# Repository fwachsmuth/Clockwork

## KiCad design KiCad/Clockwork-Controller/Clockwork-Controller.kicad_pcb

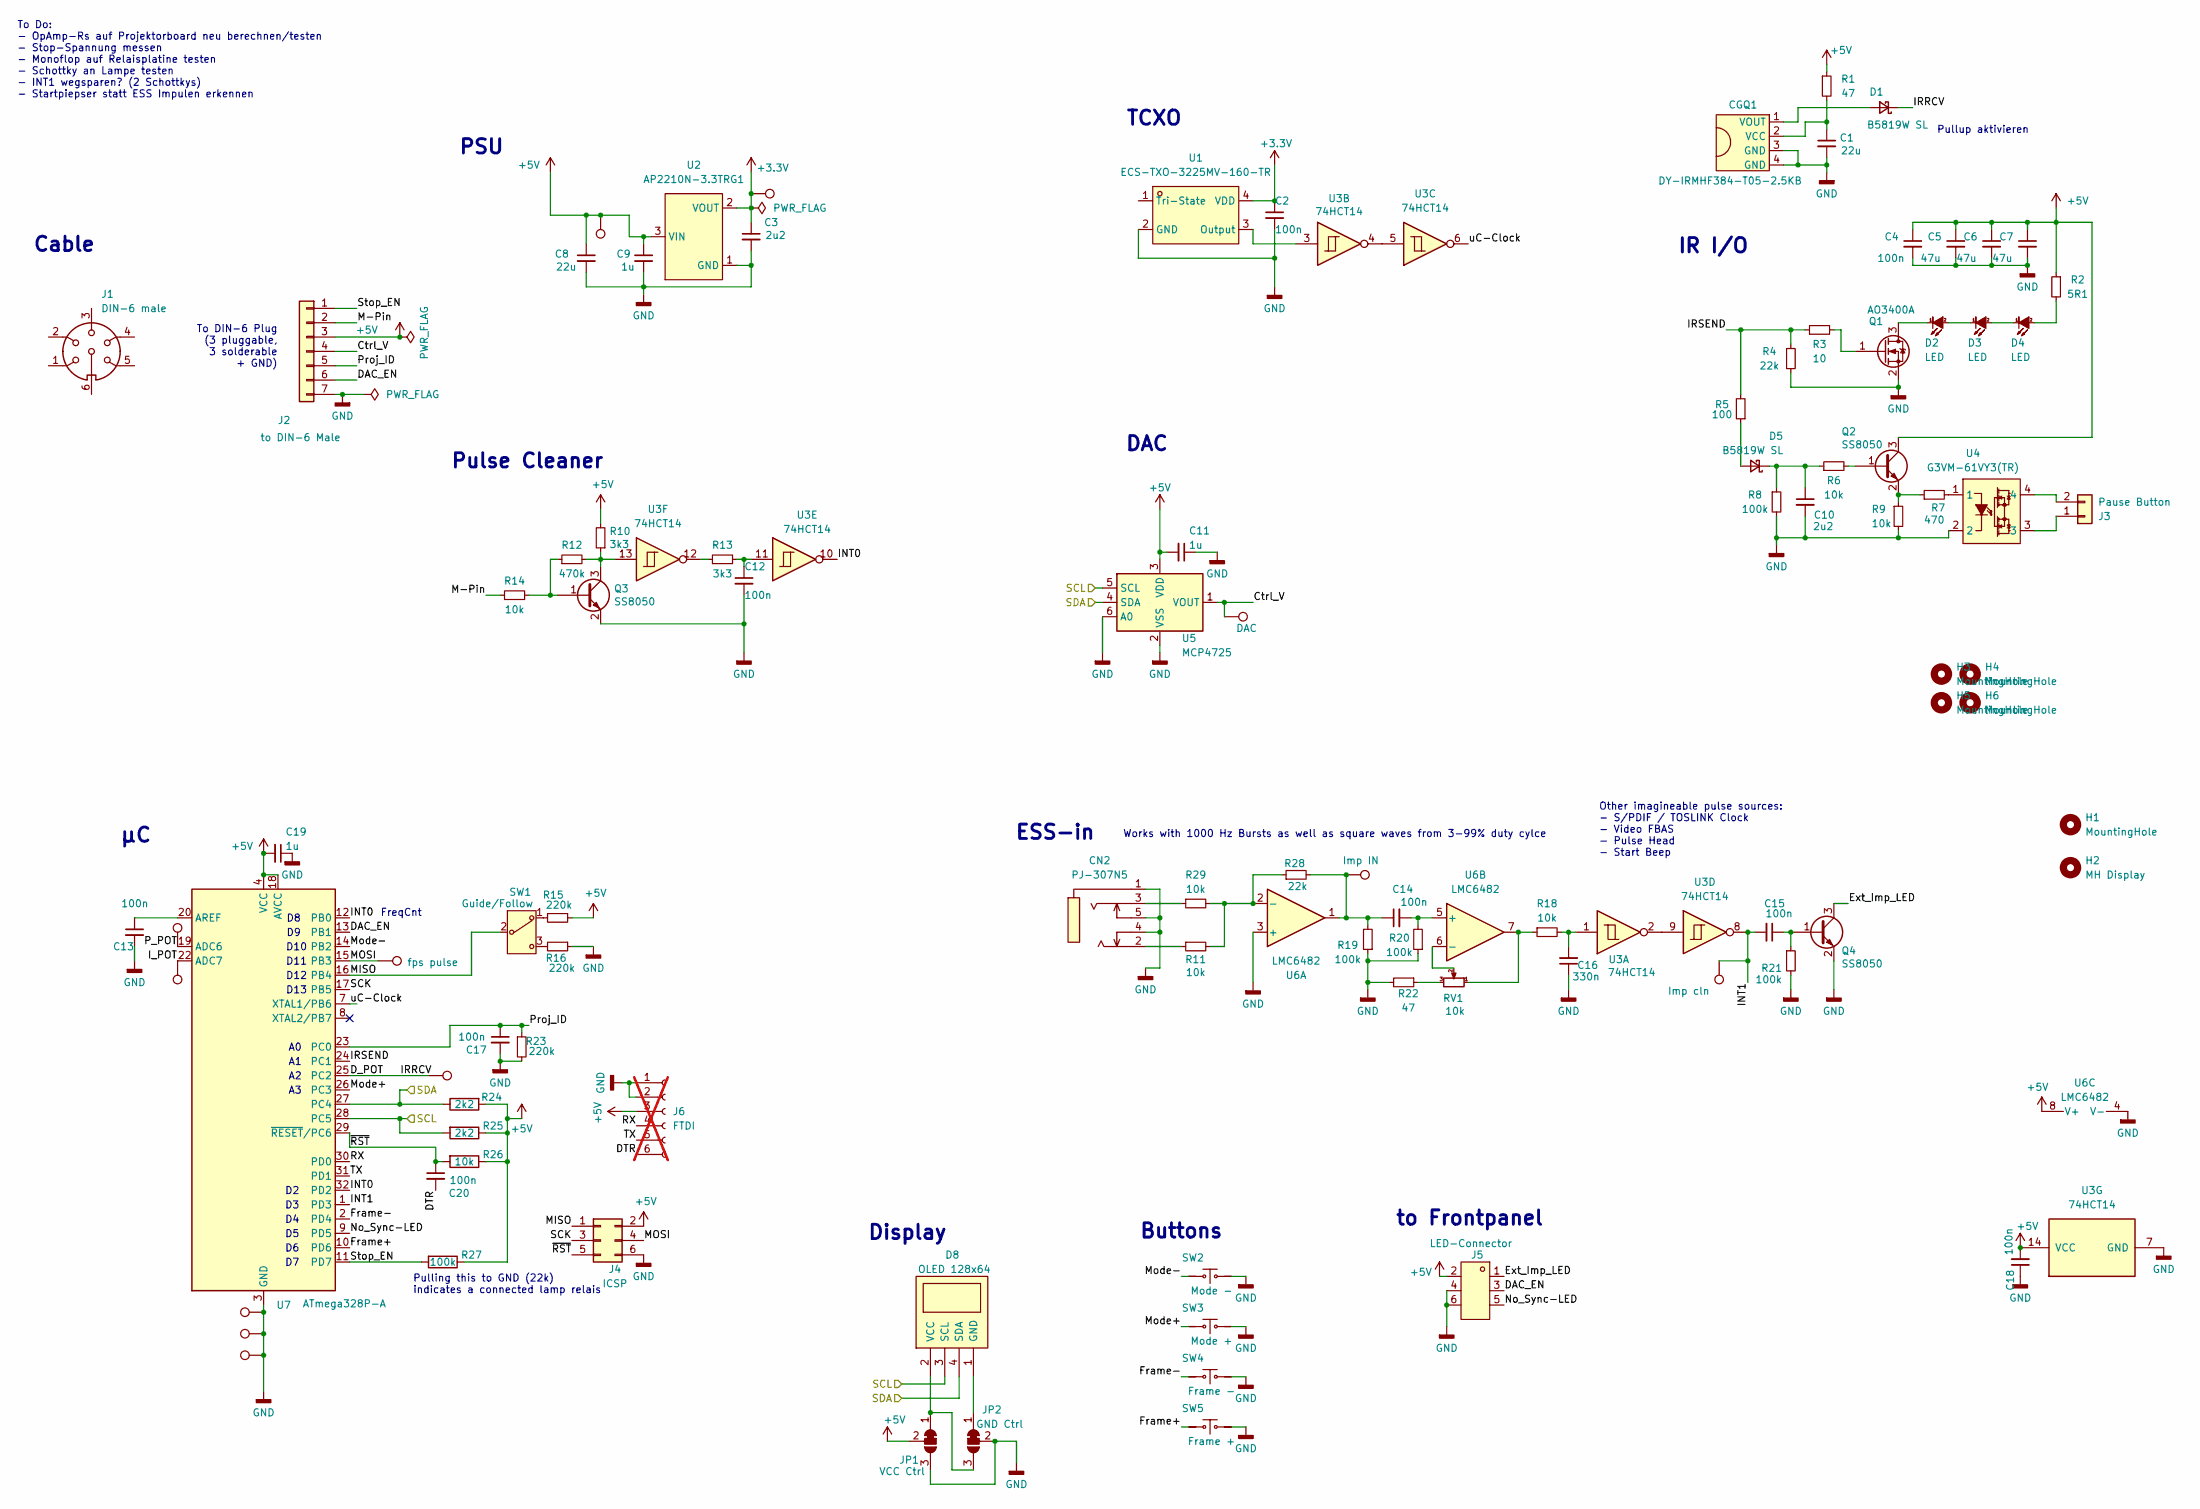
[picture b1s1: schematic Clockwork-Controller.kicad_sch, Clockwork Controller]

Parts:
C1, C8: 22u; C_0805_2012Metric; LCSC C45783
C2, C4, C12, C13, C14, C15, C17, C18, C20: 100n; C_0603_1608Metric; LCSC C14663
C3, C10: 2u2; C_0603_1608Metric; LCSC C23630
C5, C6, C7: 47u; C_1206_3216Metric; LCSC C15008
C9, C11, C19: 1u; C_0603_1608Metric; LCSC C15849
C16: 330n; C_0603_1608Metric; LCSC C1615
CGQ1: DY-IRMHF384-T05-2.5KB; OPTO-SMD_4P-L3.9-W3.4_IRM-H432M3-R8; LCSC Part C7280961
CN2: PJ-307N5; AUDIO-TH_PJ-307N5; LCSC Part C692542
D1, D5: B5819W SL; D_SOD-123; LCSC C8598
D2, D3, D4: LED; LED-SMD_XYC-IRA4335A65-X4; LCSC C2920776
D8: OLED 128x64; HDR-TH_4P-P2.54-V-F; LCSC C42163122
H1: MountingHole; Kabelbinder 4mm
H2: MH Display; MountingHole_2.2mm_M2_DIN965
H3, H4, H5, H6: MountingHole; MountingHole_3.2mm_M3_DIN965
J1: DIN-6 male
J2: to DIN-6 Male; CONN-TH_S7B-XH-A-LF-SN; LCSC C157916
J3: Pause Button; CONN-TH_2P-P2.54_MX128-2.54-GN01-02P-CU-Y-A; LCSC C918120
J4: ICSP; PinHeader_2x03_P2.54mm_Vertical_displaced
J5: LED-Connector; HDR-TH_6P-P2.00-V-F-R2-C3-S2.00-2; LCSC C7499367
J6: FTDI; PinHeader_1x06_P2.54mm_Vertical; not fitted
JP1: VCC Ctrl; SolderJumper-3_P1.3mm_Bridged2Bar12_RoundedPad1.0x1.5mm
JP2: GND Ctrl; SolderJumper-3_P1.3mm_Bridged2Bar12_RoundedPad1.0x1.5mm
Q1: AO3400A; SOT-23; LCSC C20917
Q2, Q3, Q4: SS8050; SOT-23; LCSC C2146
R1, R22: 47; R_0603_1608Metric; LCSC C23182
R2: 5R1; R_0805_2012Metric; LCSC C17724
R3: 10; R_0603_1608Metric; LCSC C22859
R4, R28: 22k; R_0603_1608Metric; LCSC C31850
R5: 100; R_0603_1608Metric; LCSC C22775
R6, R9, R11, R14, R18, R26, R29: 10k; R_0603_1608Metric; LCSC C25804
R7: 470; R_0603_1608Metric; LCSC C23179
R8, R19, R20, R21, R27: 100k; R_0603_1608Metric; LCSC C25803
R10, R13: 3k3; R_0603_1608Metric; LCSC C22978
R12: 470k; R_0603_1608Metric; LCSC C23178
R15, R16, R23: 220k; R_0603_1608Metric; LCSC C22961
R24, R25: 2k2; R_0603_1608Metric; LCSC C4190
RV1: 10k; RES-SMD_RK10J11R0A0H_fixed; LCSC C470766
SW1: Guide/Follow; SW-TH_SS-12D11G4R; LCSC C843370
SW2: Mode -; SW-SMD_4P-L6.0-W6.0-P4.50-LS9.0-H11.5; LCSC C455123
SW3: Mode +; SW-SMD_4P-L6.0-W6.0-P4.50-LS9.0-H11.5; LCSC C455123
SW4: Frame -; SW-SMD_4P-L6.0-W6.0-P4.50-LS9.0-H11.5; LCSC C455123
SW5: Frame +; SW-SMD_4P-L6.0-W6.0-P4.50-LS9.0-H11.5; LCSC C455123
TP1: 3V3; TestPoint_THTPad_1.5x1.5mm_Drill0.7mm
TP2: 5V; TestPoint_THTPad_1.5x1.5mm_Drill0.7mm
TP3, TP4, TP12: GND; TestPoint_THTPad_1.5x1.5mm_Drill0.7mm
TP5: DAC; TestPoint_THTPad_1.5x1.5mm_Drill0.7mm
TP6: P; TestPoint_THTPad_1.5x1.5mm_Drill0.7mm
TP7: I; TestPoint_THTPad_1.5x1.5mm_Drill0.7mm
TP8: fps pulse; TestPoint_THTPad_1.5x1.5mm_Drill0.7mm
TP9: Imp IN; TestPoint_THTPad_1.5x1.5mm_Drill0.7mm
TP10: Imp cln; TestPoint_THTPad_1.5x1.5mm_Drill0.7mm
TP11: D; TestPoint_THTPad_1.5x1.5mm_Drill0.7mm
U1: ECS-TXO-3225MV-160-TR; Crystal_SMD_3225-4Pin_3.2x2.5mm; LCSC C2442664
U2: AP2210N-3.3TRG1; SOT-23-3; LCSC Part C155508
U3: 74HCT14; TSSOP-14_4.4x5mm_P0.65mm; LCSC C5968
U4: G3VM-61VY3(TR); SOP-4_L3.9-W4.4-P2.54-LS7.0-BR; LCSC Part C2152318
U5: MCP4725; SOT-23-6; LCSC C144198
U6: LMC6482; SOIC-8_3.9x4.9mm_P1.27mm; LCSC C12620
U7: ATmega328P-A; TQFP-32_7x7mm_P0.8mm; LCSC C14877

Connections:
+3.3V: C2.1, C3.1, TP1.1, U1.4 (VDD), U2.2 (VOUT)
+5V: C4.1, C5.1, C6.1, C7.1, C8.1, C9.1, C11.2, C18.2, C19.2, J2.3, J4.2, J5.2, J6.3, JP1.2 (C), Q2.3 (C), R1.1, R2.1, R10.2, R15.1, R24.2, R25.1, R26.1, R27.1, TP2.1, U2.3 (VIN), U3.14 (VCC), U5.3 (VDD), U6.8 (V+), U7.4 (VCC), U7.6 (VCC), U7.18 (AVCC)
/Ctrl_V: J2.4, TP5.1, U5.1 (VOUT)
/DAC_EN: J2.6, J5.3, U7.13 (PB1)
/DTR: C20.2, J6.6
/D_POT: D1.1 (K), TP11.1, U7.25 (PC2)
/Ext_Imp_LED: J5.1, Q4.3 (C)
/Frame+: SW5.1, SW5.2, U7.10 (PD6)
/Frame-: SW4.1, SW4.2, U7.2 (PD4)
/INT0: U3.10, U7.12 (PB0), U7.32 (PD2)
/INT1: C15.2, TP10.1, U3.8, U7.1 (PD3)
/IRSEND: R3.1, R4.1, R5.2, U7.24 (PC1)
/I_POT: TP7.1, U7.22 (ADC7)
/M-Pin: J2.2, R14.1
/MISO: J4.1, SW1.2, U7.16 (PB4)
/MOSI: J4.4, TP8.1, U7.15 (PB3)
/Mode+: SW3.1, SW3.2, U7.26 (PC3)
/Mode-: SW2.1, SW2.2, U7.14 (PB2)
/No_Sync-LED: J5.5, U7.9 (PD5)
/P_POT: TP6.1, U7.19 (ADC6)
/Proj_ID: C17.1, J2.5, R23.1, U7.23 (PC0)
/RX: J6.4, U7.30 (PD0)
/SCK: J4.3, U7.17 (PB5)
/SCL: D8.3 (SCL), R25.2, U5.5 (SCL), U7.28 (PC5)
/SDA: D8.4 (SDA), R24.1, U5.4 (SDA), U7.27 (PC4)
/Stop_EN: J2.1, R27.2, U7.11 (PD7)
/TX: J6.5, U7.31 (PD1)
/uC-Clock: U3.6, U7.7 (XTAL1/PB6)
/~RST: C20.1, J4.5, R26.2, U7.29 (~RESET/PC6)
GND: C1.2, C2.2, C3.2, C4.2, C5.2, C6.2, C7.2, C8.2, C9.2, C10.2, C11.1, C12.2, C13.2, C16.1, C17.2, C18.1, C19.1, CGQ1.3 (GND), CGQ1.4 (GND), CN2.1, CN2.4, CN2.5, J2.7, J4.6, J5.4, J5.6, J6.1, J6.2, JP1.3 (B), JP2.2 (C), Q1.2 (S), Q3.2 (E), Q4.2 (E), R4.2, R8.2, R9.2, R16.1, R19.1, R20.1, R21.2, R22.2, R23.2, SW2.3, SW2.4, SW3.3, SW3.4, SW4.3, SW4.4, SW5.3, SW5.4, TP3.1, TP4.1, TP12.1, U1.2 (GND), U2.1 (GND), U3.7 (GND), U4.2, U5.2 (VSS), U5.6 (A0), U6.3 (+), U6.4 (V-), U7.3 (GND), U7.5 (GND), U7.21 (GND)
unnamed: C12.1, R13.2, U3.11
unnamed: C14.1, R19.2, R28.2, TP9.1, U6.1
unnamed: C16.2, R18.2, U3.1
unnamed: C1.1, CGQ1.2 (VCC), R1.2
unnamed: CGQ1.1 (VOUT), D1.2 (A)
unnamed: CN2.2, R11.1
unnamed: CN2.3, R29.1
unnamed: D2.2 (A), D3.1 (K)
unnamed: D2.1 (K), Q1.3 (D)
unnamed: D3.2 (A), D4.1 (K)
unnamed: D4.2 (A), R2.2
unnamed: D5.2 (A), R5.1
unnamed: C10.1, D5.1 (K), R6.1, R8.1
unnamed: D8.1 (GND), JP2.1 (A)
unnamed: D8.2 (VCC), JP1.1 (A), JP2.3 (B)
unnamed: J3.1, U4.3
unnamed: J3.2, U4.4
unnamed: Q1.1 (G), R3.2
unnamed: Q2.1 (B), R6.2
unnamed: Q2.2 (E), R7.1, R9.1
unnamed: Q3.1 (B), R12.1, R14.2
unnamed: Q3.3 (C), R10.1, R12.2, U3.13
unnamed: C15.1, Q4.1 (B), R21.1
unnamed: R7.2, U4.1
unnamed: R13.1, U3.12
unnamed: R15.2, SW1.1
unnamed: R16.2, SW1.3
unnamed: R18.1, RV1.1, U6.7
unnamed: R22.1, RV1.3
unnamed: U1.3 (Output), U3.3
unnamed: U3.2, U3.9
unnamed: U3.4, U3.5
unnamed: R11.2, R28.1, R29.2, U6.2 (-)
unnamed: C14.2, R20.2, U6.5 (+)
unnamed: RV1.2, U6.6 (-)
unnamed: C13.1, U7.20 (AREF)

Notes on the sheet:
D10
Pullup aktivieren
Display
Other imagineable pulse sources: - S/PDIF / TOSLINK Clock - Video FBAS - Pulse Head - Start Beep
D13
Buttons
to Frontpanel
Pulling this to GND (22k) indicates a connected lamp relais
To Do: - OpAmp-Rs auf Projektorboard neu berechnen/testen - Stop-Spannung messen - Monoflop auf Relaisplatine testen - Schottky an Lampe testen - INT1 wegsparen? (2 Schottkys) - Startpiepser statt ESS Impulen erkennen
Pulse Cleaner
Cable
D11
TCXO
DAC
Works with 1000 Hz Bursts as well as square waves from 3-99% duty cylce
FreqCnt
ESS-in
PSU
D12
To DIN-6 Plug (3 pluggable, 3 solderable + GND)
IR I/O

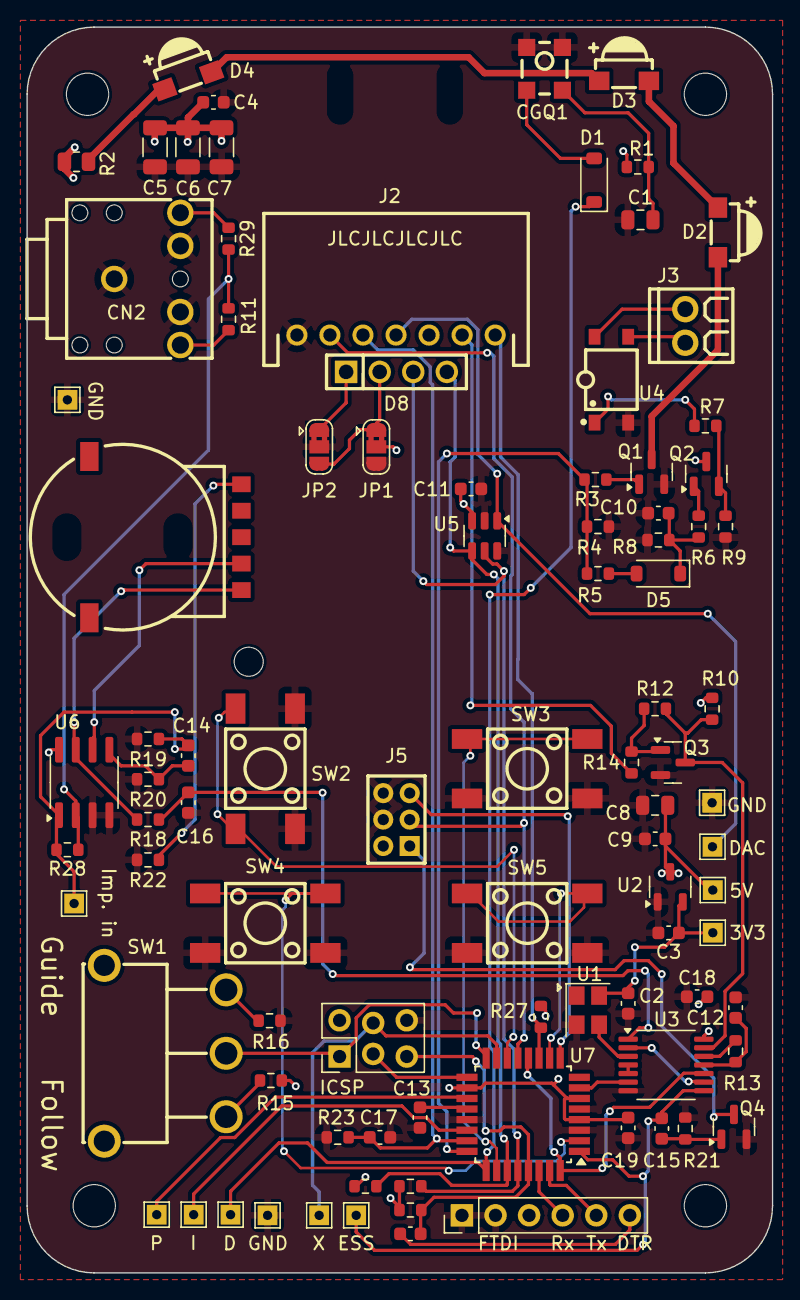
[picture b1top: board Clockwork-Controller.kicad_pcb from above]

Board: 2 copper layers, 56.4 x 94.2 mm, 98 parts (0 on the bottom side), 66 nets.

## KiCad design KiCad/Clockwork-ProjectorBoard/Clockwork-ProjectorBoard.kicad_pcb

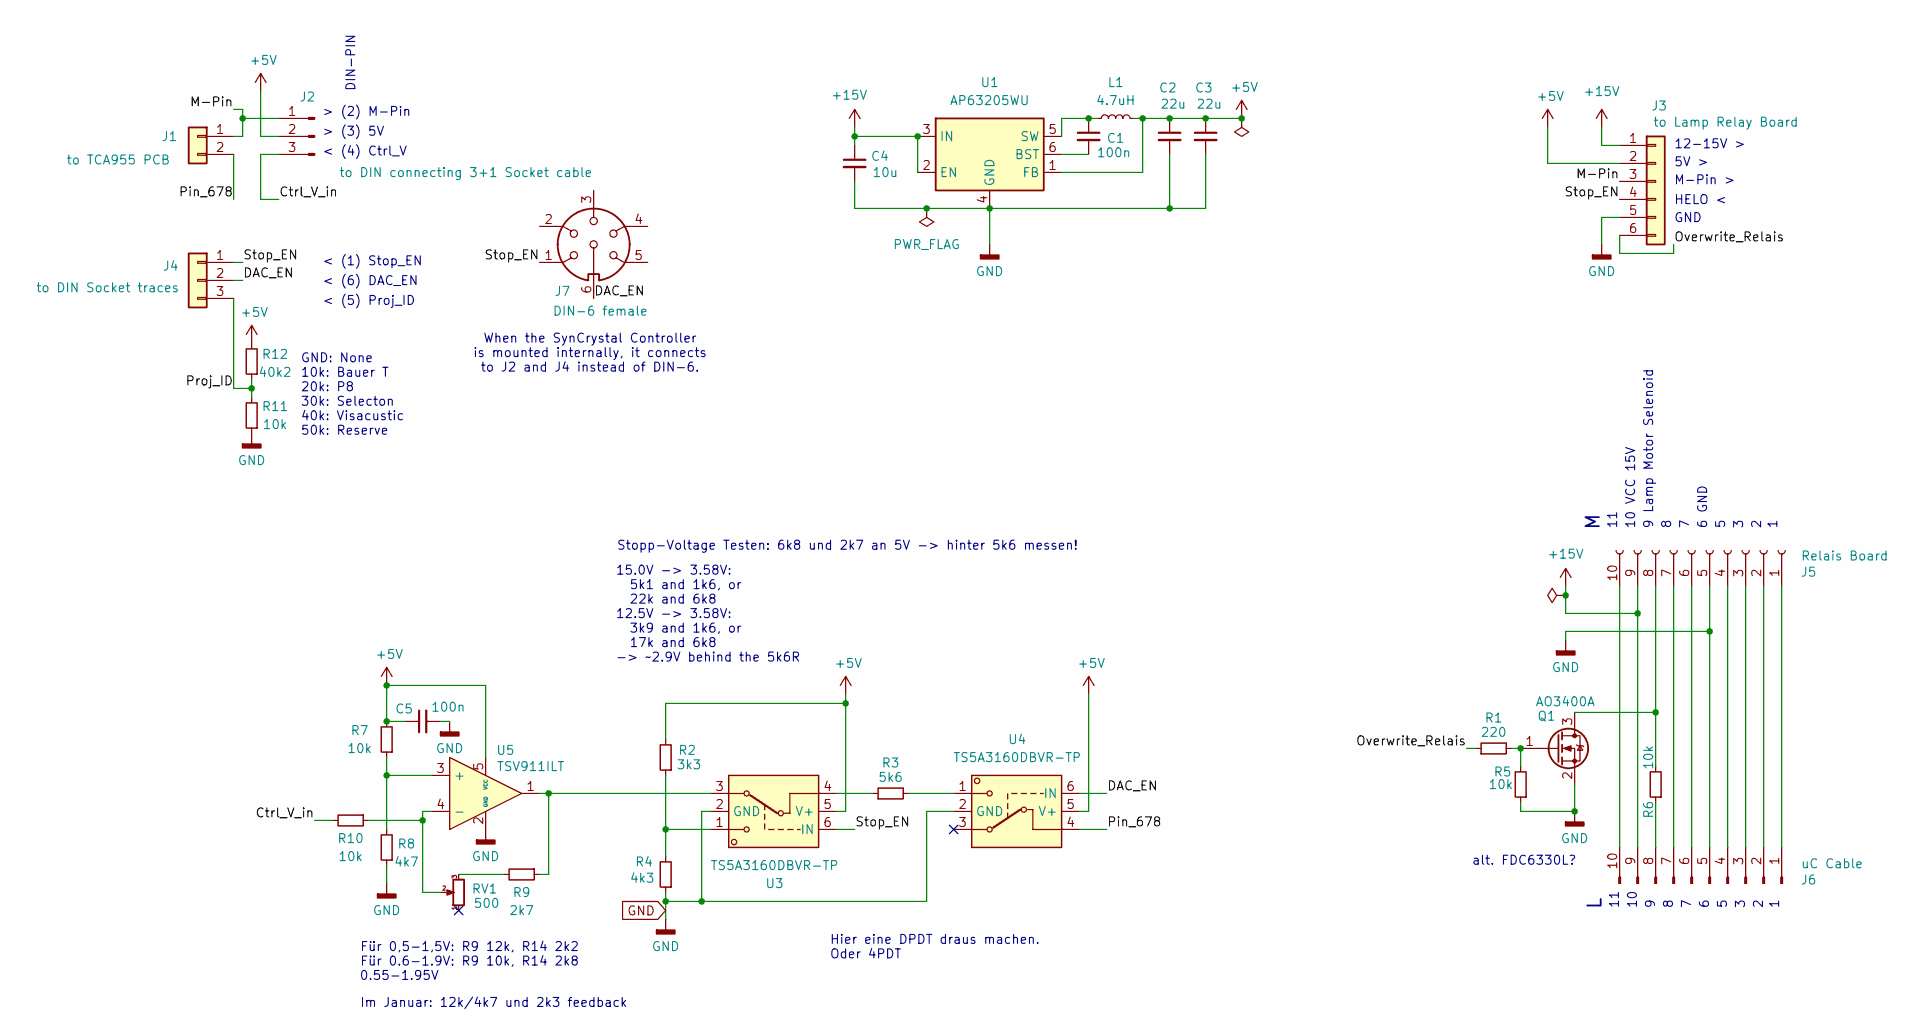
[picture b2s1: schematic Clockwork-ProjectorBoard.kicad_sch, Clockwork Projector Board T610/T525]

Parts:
C1, C5: 100n; C_0603_1608Metric; LCSC C14663
C2, C3: 22u; C_0603_1608Metric; LCSC C45783
C4: 10u; C_0603_1608Metric; LCSC C15850
J1: to TCA955 PCB; CONN-TH_2P-P2.54_ZX-XH2.54-2PZZ-Y; LCSC C22388684
J2: to DIN connecting 3+1 Socket cable; PinHeader_1x03_P2.54mm_Vertical_BAUER; LCSC C6332196
J3: to Lamp Relay Board; CONN-TH_6P-P2.54_ZX-XH2.54-6PZZ-R; LCSC C22388628
J4: to DIN Socket traces; CONN-TH_ZX-XH2.54-3PZZ-Y; LCSC C22388685
J5: Relais Board; HDR-TH_10P-P2.54-H-F-W10.0-N; LCSC C2897392
J6: uC Cable; HDR-TH_10P-P2.54-H-M-W10.4_flipped; LCSC C3012231
J7: DIN-6 female
L1: 4.7uH; IND-SMD_L3.0-W3.0; LCSC C527613
Q1: AO3400A; SOT-23; LCSC C20917
R1: 220; R_0603_1608Metric; LCSC C22962
R2: 3k3; R_0603_1608Metric
R3: 5k6; R_0603_1608Metric; LCSC C23189
R4: 4k3; R_0603_1608Metric
R5, R6, R7, R10: 10k; R_0603_1608Metric; LCSC C25804
R8: 4k7; R_0603_1608Metric; LCSC C23162
R9: 2k7; R_0603_1608Metric; LCSC C13167
R11: 10k; R_0402_1005Metric; LCSC C25744
R12: 40k2; R_0402_1005Metric; LCSC C137983
RV1: 500; RES-ADJ-SMD_3P-L3.8-W3.7_VGF39NCHXT; LCSC C720649
U1: AP63205WU; TSOT-23-6; LCSC C2071056
U3, U4: TS5A3160DBVR-TP; SOT-23-6_L2.9-W1.6-P0.95-LS2.8-BR; LCSC C42411033
U5: TSV911ILT; SOT-23-5_L2.9-W1.6-P0.95-LS2.8-BR; LCSC C672321

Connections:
+5V: C2.1, C3.1, C5.1, J2.2, J3.2, L1.2, R2.2, R7.2, R12.2, U1.1 (FB), U3.5 (V+), U4.5 (V+), U5.5 (VCC)
+15V: C4.1, J3.1, J5.9, J6.9, U1.2 (EN), U1.3 (IN)
/Ctrl_V_in: J2.3, R10.2
/DAC_EN: J4.2, J7.6, U4.6 (IN)
/M-Pin: J1.1, J2.1, J3.3
/Overwrite_Relais: J3.6, R1.1
/Pin_678: J1.2, U4.4
/Proj_ID: J4.3, R11.2, R12.1
/Stop_EN: J3.4, J4.1, J7.1, U3.6 (IN)
GND: C2.2, C3.2, C4.2, C5.2, J3.5, J5.5, J6.5, Q1.2 (S), R4.1, R5.1, R8.1, R11.1, U1.4 (GND), U3.2 (GND), U4.2 (GND), U5.2 (GND)
unnamed: J5.1, J6.1
unnamed: J5.2, J6.2
unnamed: J5.3, J6.3
unnamed: J5.4, J6.4
unnamed: J5.6, J6.6
unnamed: J5.7, J6.7
unnamed: J5.8, Q1.3 (D), R6.2
unnamed: J5.10, J6.10
unnamed: J6.8, R6.1
unnamed: Q1.1 (G), R1.2, R5.2
unnamed: R2.1, R4.2, U3.1
unnamed: R3.1, U3.4
unnamed: R3.2, U4.1
unnamed: R9.1, U3.3, U5.1
unnamed: R9.2, RV1.3
unnamed: C1.2, U1.6 (BST)
unnamed: C1.1, L1.1, U1.5 (SW)
unnamed: R7.1, R8.2, U5.3 (+)
unnamed: R10.1, RV1.2, U5.4 (-)

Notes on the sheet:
Hier eine DPDT draus machen. Oder 4PDT
5V >
0.55-1.95V
M-Pin >
Für 0,5-1,5V: R9 12k, R14 2k2 Für 0.6-1.9V: R9 10k, R14 2k8
HELO <
When the SynCrystal Controller is mounted internally, it connects to J2 and J4 instead of DIN-6.
6 GND
> (3) 5V
< (6) DAC_EN
Im Januar: 12k/4k7 und 2k3 feedback
> (2) M-Pin
DIN-PIN
GND: None 10k: Bauer T 20k: P8 30k: Selecton 40k: Visacustic 50k: Reserve
10 VCC 15V
< (5) Proj_ID
alt. FDC6330L?
< (4) Ctrl_V
15.0V -> 3.58V: 5k1 and 1k6, or 22k and 6k8 12.5V -> 3.58V: 3k9 and 1k6, or 17k and 6k8 -> ~2.9V behind the 5k6R
< (1) Stop_EN
GND
12-15V >
9 Lamp Motor Selenoid
Stopp-Voltage Testen: 6k8 und 2k7 an 5V -> hinter 5k6 messen!

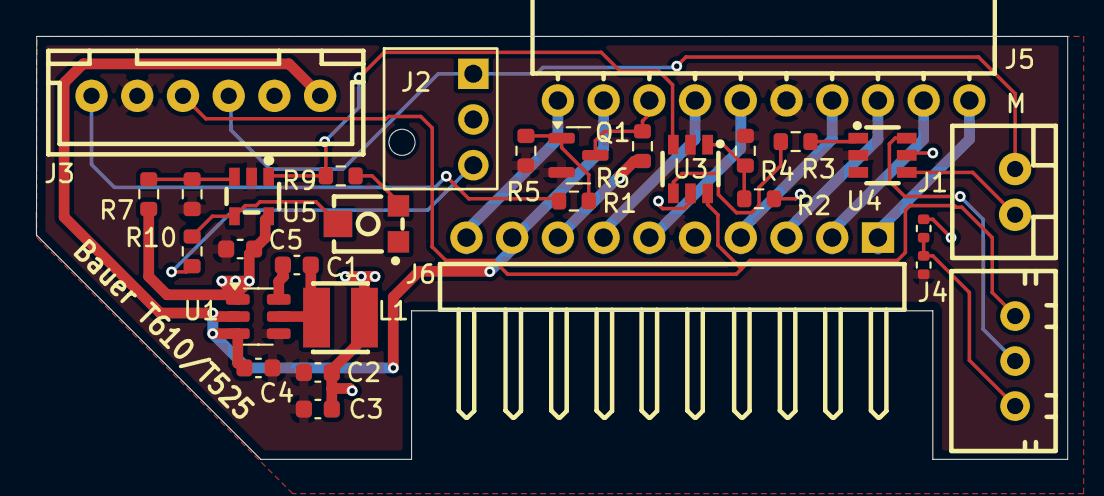
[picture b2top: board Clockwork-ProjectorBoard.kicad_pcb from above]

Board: 2 copper layers, 57.3 x 23.5 mm, 30 parts (0 on the bottom side), 29 nets.

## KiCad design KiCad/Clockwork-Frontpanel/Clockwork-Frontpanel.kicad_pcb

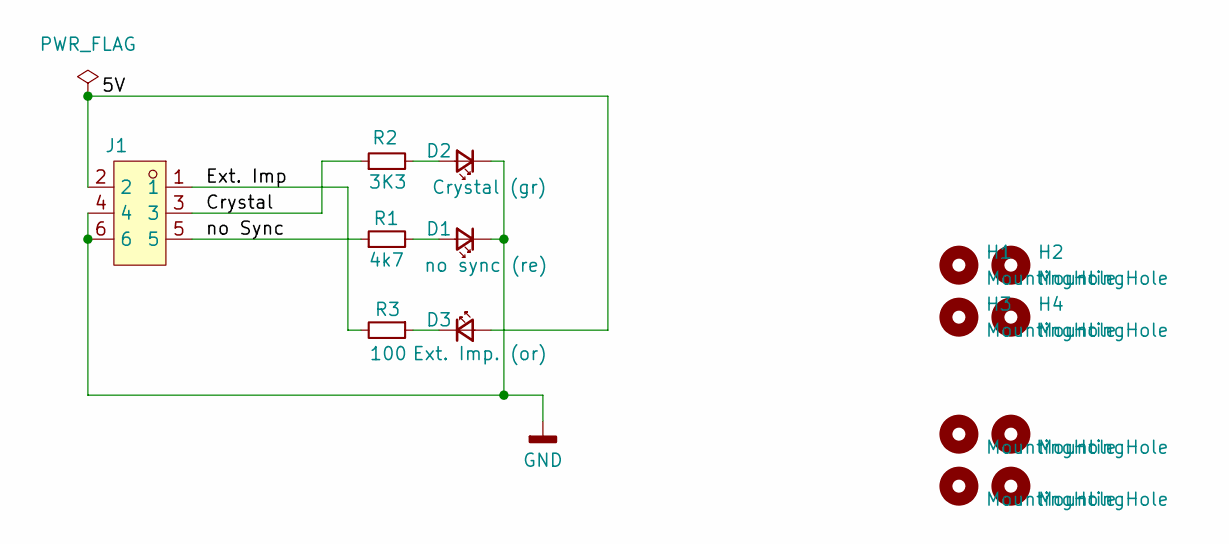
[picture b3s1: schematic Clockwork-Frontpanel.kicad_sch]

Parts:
D1: no sync (re); LED-SMD_L3.2-W1.6-RD-EH-3_kicad; LCSC C2892757
D2: Crystal (gr); LED-SMD_L3.2-W1.6-RD-EH-3_kicad; LCSC C2980185
D3: Ext. Imp. (or); LED-SMD_L3.2-W1.6-RD-EH-3_kicad; LCSC C424133
H1, H2, H3, H4: MountingHole; MountingHole_3.2mm_M3_DIN965
H5, H6, H7, H8: MountingHole; MountingHole_3.5mm_M3
J1: HDR-SMD_6P-P2.00-V-M-R2-C3-LS6.5_flipped; LCSC Part C3294482
R1: 4k7; R_0603_1608Metric
R2: 3K3; R_0603_1608Metric; LCSC C22978
R3: 100; R_0603_1608Metric

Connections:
/5V: D3.2 (A), J1.2
/Crystal: J1.3, R2.1
/Ext. Imp: J1.1, R3.2
/no Sync: J1.5, R1.1
GND: D1.1 (K), D2.1 (K), J1.4, J1.6
unnamed: D1.2 (A), R1.2
unnamed: D2.2 (A), R2.2
unnamed: D3.1 (K), R3.1

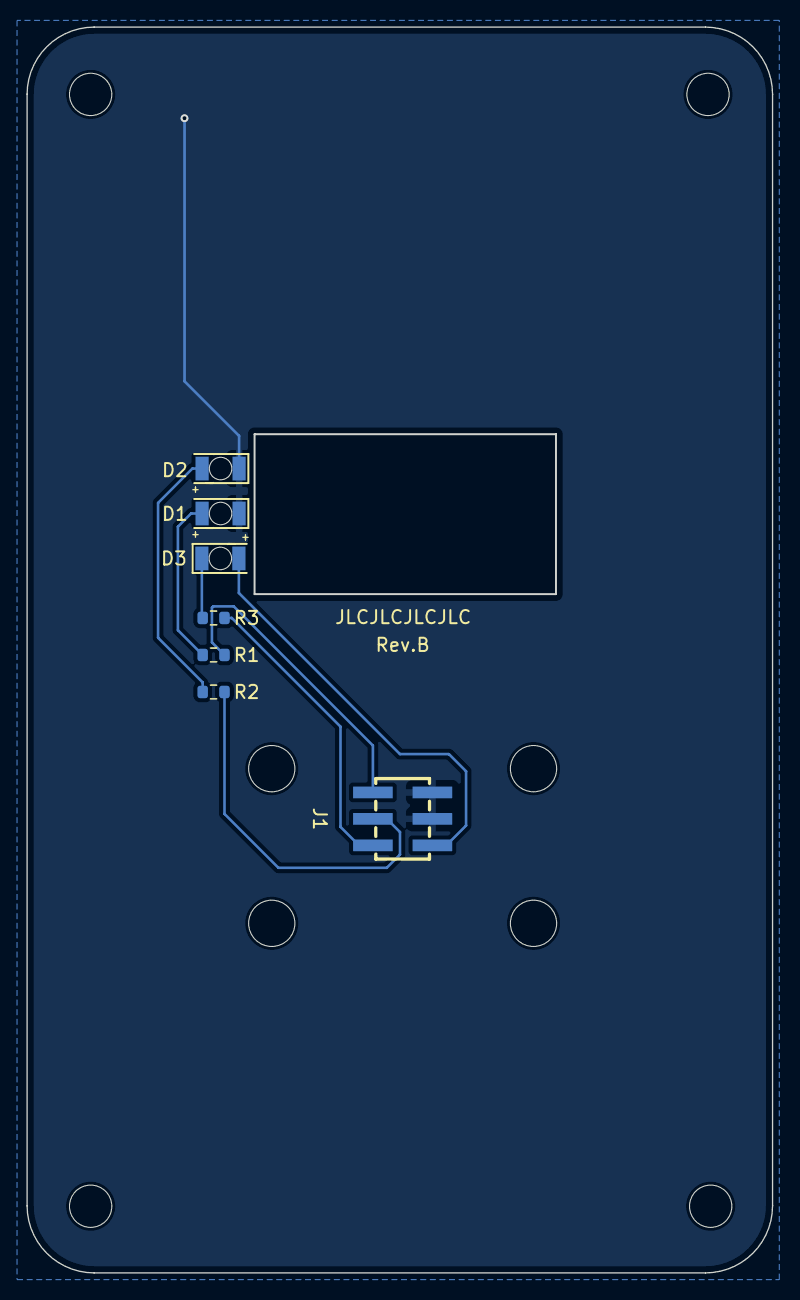
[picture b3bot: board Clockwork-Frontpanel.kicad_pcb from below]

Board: 2 copper layers, 56.4 x 94.2 mm, 15 parts (7 on the bottom side), 8 nets.

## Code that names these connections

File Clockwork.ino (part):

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    Follow INT1 count, not the timer_pulses
    Detect Follow/Guide Switch position
    If Follow:
        Enable STOP_EN_PIN
        On first Impulse, Disable STOP_EN_PIN
    If Guide:
        On first Impulse, send learned IR code
    FreqMeasure (like in Auto Mode)
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

// pin consts
const byte SHAFT_PULSE_PIN = 2;  // aka INT0
const byte LED_RED_PIN = 5; //  Out of Sync
const byte FPS_PULSE_OUT_PIN = 11; //  12 on breadboard. Pulse when Crystal is enabled. Todo: This still needs to be coded
const byte DAC_ENABLE_PIN = 9;
const byte AUDIOMODE_SWITCH_PIN = 12;
const byte STOP_EN_PIN = 7; // Flipping this HIGH stops the projector if DAC_ENABLE_PIN is HIGH too
const byte LAMP_RELAY_DETECT_PIN = 7; // The same pin (in input mode) reflects if a Lamp Relais Board is connected
const byte PROJ_ID_PIN = A0; // This is used to detect the projector type, if one is connected

const byte LEFT_BTTN_PIN = 10;
const byte RIGHT_BTTN_PIN = A3;     // 13 on breadboard
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    pinMode(CATCH_UP_BTTN_PIN, INPUT_PULLUP);
    pinMode(AUDIOMODE_SWITCH_PIN, INPUT); // This is used to read the Follow/Guide switch
    pinMode(DAC_ENABLE_PIN, OUTPUT);
    pinMode(PROJ_ID_PIN, INPUT);

    // Let's read the projector board's voltage divider to detect the projector type.
    int adcValue = analogRead(PROJ_ID_PIN);
    ProjectorType proj = detectProjector(adcValue);

    // Copy the projector config for the detected type
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        }
    }
    // Configure Pin 7 as OUTPUT again, allowing us to stop the projector
    pinMode(STOP_EN_PIN, OUTPUT);
    digitalWrite(STOP_EN_PIN, LOW); 

    // Use this for PID tuning with Pots
    // pinMode(P_PIN, INPUT);
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    {
        timer_pulses++;    // Increment timer_pulses
        timer_modulus = 0; // Reset the counter
        // PIND |= (1 << 7); // Toggle pin 7 (I guess this was used for debugging. It now conflicts with the STOP_EN_PIN)
    }
    // Dither logic (fixed-point accumulator)
    dither_accumulator_32 += speed.dither_frac32;
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
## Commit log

2019-11-16 Initial Code Commit
2019-11-17 First Button attempt
2019-11-17 Better Button Handling
2019-11-24 Adding Switch Library from Nick Gammon
2019-11-24 First u8g2 output, yay
2019-11-27 More beuaty
2019-12-28 Merging Todos
2024-12-21 Adding .gitignore
2024-12-21 Starting fresh, it's been too long ago
2024-12-21 Initial KiCad thoughts
2024-12-21 removing duplicate ino file
2024-12-23 a working but far too senistive implementation of the speedswitch detection. Measuere 24 times per revolution...
2024-12-24 speed reliable detected 8 frames after projector start...
2024-12-24 ignore build cache
2024-12-24 72 impulses (6 revolutions) is better than 8...
2024-12-24 Better: 48 frames to determine speed :)
2024-12-24 use insertion sort instead of qsort — saves 950B of program storage and should also be faster with just 12 items
2024-12-25 rename some vars for clarity
2024-12-26 initial stop detection
2024-12-26 this works pretty well... but needs cleanup.
2024-12-26 cleaned up
2024-12-26 make runstate a bool
2024-12-26 Cleanup and more robust (yet slightly slower) stability detection. It really doesn't matter though.
2024-12-26 fixing initial run state
2024-12-27 saving the guesstimated speed to a global var
2024-12-27 using Timer2 instead of micros()
2024-12-28 read and calculate speed diffs
2024-12-28 This is a good start.
2024-12-28 the opamp
2024-12-28 a wonderfully working PID controller, roughly tuned
2024-12-29 variable name refactoring
2024-12-29 cleanup and adding todos
2024-12-29 better tuned
2024-12-29 yet better tuning
2024-12-29 a bit less aggressive, yet more stable
2024-12-29 adding 24 fps support. resetting the dac after a detected stop
2024-12-29 stop measuring running freq once we have found a switch pos (until the projector stops)
2024-12-29 fixes initing the PID with initial values both on start as well as inbetween projector runs
2024-12-29 fixes overshooting on subsequent projector runs due to false PID computations in a race condition (shaft stil breaking timer fired already before stop detection)
2024-12-29 All comments in english. Yay!
2024-12-29 Let's add some buttons
2024-12-29 adds push buttons, starts measuring DAC value lifetime
2024-12-29 adds better dac value lifecycle management
2024-12-29 add some eeprom helpers
2024-12-30 more eeprom tooling
2024-12-30 PID is running more often (Nyquist) but less aggressive for a smootehr run. Consider a two-stage PID later.
2024-12-30 Removing all the EPROM Foo. All we need is a faster (or adaptive) PID.
2024-12-30 added a switch to pin 9 to connect/disconnect the overlay voltage
2024-12-30 adding switch to kicad
2024-12-30 gitignore
2024-12-31 Initial speed selector state machine
2024-12-31 Partila Button handling, but this ancient SwitchManager is coming to its limits...
2025-01-01 Correct Button handling, yay
2025-01-01 more elegant mode selection
2025-01-01 4 Buttons is so much better than just two. Longpresses are just not intuitive.
2025-01-01 Move setup() and loop() to top
2025-01-01 Adds support to catch-up / drop-back a frame or three
2025-01-02 Timer1 wip
2025-01-02 dithering timers to wuthering heights
2025-01-02 Found configs for all target speeds with 0 ppm :)
2025-01-02 some cleanup
2025-01-02 helper
2025-01-02 more helpers
2025-01-02 refined timer configs
2025-01-02 allow re-entering auto mode. Not perfect yet...
2025-01-02 Refactored (or introduced?) a better FSM
2025-01-03 Speed Lock LED; this wil go on the display tho
2025-01-03 Timeout-based stop detection, and moved out of the ISR
2025-01-03 clean up, saving a bit of memory, adding structural notes
2025-01-03 a few optimizations. Stable!
2025-01-03 speed change broken
2025-01-03 this works again
2025-01-03 new bug: can't return to auto
2025-01-03 fixes auto-reentry. still puurging the pulsediff on speed change though
2025-01-03 Fixes Speed Transitions while the projector is running
2025-01-03 updating todos
2025-01-03 saving state with old median based measurement
2025-01-04 First FreqMeasure-based run detection, still freewheeling though — second start is hence measuered wrong.
2025-01-04 Fully refactored run retection. Uses 54% of Progmem and 1485 bytes of global vars
2025-01-04 removing dead code: 16298 B progmem, 1281 B global vars
2025-01-04 Stremalined var type declarations, masked fps9 mode to shave off 7 bytes of RAM (16232 progmem, 1275 dynamic mem)
2025-01-04 Use F() macro to get RAM usage down to 1085 B
2025-01-04 adding a button helper
2025-01-04 Comments, function renaming
2025-01-04 prep work for sepmag-comaptible speed switching
2025-01-04 interim state with new sepmag pulse keeping at speed changes. does not survive auto/none modes yet, and somehow speed changes do not create an approriate error yet.
2025-01-05 wip, but fixed some VERY nasty bugs where pulse and frames were mixed up
2025-01-05 Biggest bug fixed — nned to put the timer_factor into the timer ISR to count pulses correctly
2025-01-05 It (mostly) works again. I have no idea though why resetting the timer_modulus in the SetupTimer1forFps() caused that the modulus never incremented beyond 1 in the timer ISR.
2025-01-05 changes stop_detection back to micros. On start we are still seeing 4 wrong stops in the first second.
2025-01-05 remove dead comments
2025-01-05 Fixes the lag on start by passing on the freqMeasured frames as timer_pulses offset. Also removed the "both ISR updated" sempahores since the made a lot of headaches
2025-01-05 Restore stop detection
2025-01-06 improving debug spam by watching the DAC, not the error
2025-01-06 initial adaptive pid... crazy
2025-01-06 PID-Kontrolle per Poti :)
2025-01-06 poor man's fourier
2025-01-06 PID is perfectly tuned, added code for re-tuning with pots if needed
2025-01-06 "SEPMAG mode" finally working. Introduced new bugs tho :(
2025-01-06 updated todos
2025-01-06 Lot's of celanup, no functional changes
2025-01-06 Fixing the "can't start after leaving in non-AUTO" bug
2025-01-06 We are setting the altered timer_pulse values now. Can't really confirm yet if controller keeps sync (need SMPTE timecode to verify.) However, pending errors somehow seem to add up?
2025-01-06 open bug: Cannot start correctly in a manual selected mode: somehow the DAC is pulled to 0
2025-01-06 DAC no longer pulled to 0, but to a wrong value...
2025-01-07 fixed a missing DAC enable
2025-01-07 Fixed the Manual Speed Selection. DIffering indices in structs and anums are dangerous...
2025-01-07 More debug code, but it's getting ugly
2025-01-07 Refactoring my struct to conflict less with enum indices
2025-01-07 More refactoring. This feels a lot better
2025-01-09 getting there...
2025-01-11 something (memcpy_P?) goes horribly wrong when starting in FPS_AUTO
2025-01-11 okay calling activateSpeedConfig(FPS_AUTO); twice in setup did not end well. Fixed now
2025-01-11 almost there :)
2025-01-11 timer_corection_factor calculation finally precise AND working
2025-01-11 add scope test pin on d7
2025-01-11 A good working state. Still getting stuck in NONE mode tho
2025-01-11 Refactored timer1 setup
2025-01-11 NONE Bug fixed. Re-entering a non-NONE mode still makes the projector catch up tho
2025-01-11 removes some unused vars
2025-01-12 Cleaned up loop(). Seems to work, but should be thoroughly tested
2025-01-12 yet more cleanup
2025-01-12 Todos
2025-01-12 Explainthe dithering a bit better for later me
2025-01-12 First Dispaly thingies
2025-01-12 More Display tweaking
2025-01-13 nah a scale wont work w/o u8g2
2025-01-13 Just a few layout tweaks, now using just 2 fonts
2025-01-14 idea for another func... commented out for now
2025-01-14 Skip Auto Mode when the projector is running — it makes no sense.
2025-01-14 Make the atomic time digit updating more modular
2025-01-18 Fixed base values for perfect speed acuracy
2025-01-19 pulling the schamtice together
2025-01-20 Schematics Progress
2025-01-20 ERC progress
2025-01-20 ERC clean, some pin changes for final PCB
2025-01-20 Most footprints
2025-01-23 PCB in progress
2025-01-25 More Footprint work
2025-02-01 More schematics
2025-02-02 Projector PCB!
2025-02-03 DRC for Projector Board happy
2025-02-04 Polishing up for Rev.A
2025-02-09 More changes
2025-03-02 Starting to assign part numbers
2025-03-05 Adding the OpAmp to the Projector Board, also, some LCSC Part numbers
2025-03-07 Moved the OpAmp to the Projector Board. This Layout is DRC 0, but not optimal
2025-03-07 Much better layout, DRC = 0
2025-03-10 moving the 10k OpAmp Input R to the Projector board
2025-03-14 Adding the VOltage Divider to Projector Board to allow Projector Detection. Also, fixing various footprints on the controller. ERC now failing.
2025-03-15 ERC now happy!
2025-03-15 Reannotated, PCB now messed up :)
2025-03-16 90% routed
2025-03-16 Looking good! Stil gotta run DRC
2025-03-16 DRC happy, me happy.
2025-03-24 Rev.A, orderable
2025-03-24 Renaming Project and Repo from "SynCrystal" to "ImpulsWerk"
2025-03-31 Before renaming
2025-04-02 Renaming once more
2025-04-02 Some forgotten renames
2025-04-07 New Gerbers, added the xtal to the BOM, new MH for OLED
2025-05-18 Starting Rev.B, fixing DIN-Connector-Wire Pin 2/3 to keep DIN/JST pin alignment
2025-05-28 Removing redundant R11, pulling M Pin up before reaching the Schmitt Triggers
2025-05-28 Updating some Pins for PCB
2025-05-29 Swao Ext.Imp and Sync LED
2025-05-29 Adding GND TPs
2025-05-29 Lowered J2 further towards the display to allow better cable securing
2025-05-29 Enlarging wirestrap holes (4mm)
2025-05-29 Updating BOM to use C455123 switches (11.5mm, not 8mm)
2025-05-29 Moving the 3.5mm jack inwards to be flush with the edge
2025-05-29 Enlarged J3 holes per JLC request (1.2mm)
2025-05-29 Adding FTDI port
2025-05-29 Label it Rev.B
2025-05-29 Swapping IR Tx and Rx for better reach
2025-05-29 Fixing the Pin Numbering Mess for the Frontpanel LEDs, also, polarity of ESS in LED
2025-05-29 Enable Rev.B also for the Forntpanel
2025-05-29 Updated Resistor Values, Button Holes 0.3mm bigger, Display Rect 1mm lower, new LED Labels, Moved GND Via
2025-05-29 Adjusting LED-Pins on the Controller Side (adding VCC)
2025-05-29 Potentiometer Flip for more intuitive Pulse Amp control
2025-05-29 Starting to make the Projector detections working. STOP_EN does not work as input tho due to the pulldown on the MOSFET. Maybe DAC_EN is an option when in Input mode?
2025-05-30 Adds temp code to enable STOP_EN_PIN after 15 seconds. Also, it disables the Pin 7 toggling that was still in the ISR for debug...
2025-05-30 Fixes the Voltage Divider for the STOP Voltage, which turned out too low
2025-05-31 Adding a 6th Pin to the Lamp Relais Connector, which pulls the MOSFET high, disabling the built-in Relay
2025-05-31 Optimize Projector Board Size, red socket will fit better.
2025-05-31 Optimized THT pad diameters for the connectors
2025-05-31 Adding the 6th pin to the Lamp Relay Schematic
2025-05-31 On Startup, detect if a Lamp Rela Board is connected or not
2025-05-31 Detect the connected Projector Type
2025-06-01 Using both left and right channel for ESS in
2025-06-01 Properly summing up R and L channel using the second OpAmp
2025-06-01 Prepare code to handle various differing projectors
2025-06-01 Better initial DAC values (hardocded)
2025-06-01 Set PID tuning based on projector's struct
2025-06-01 Shaving off 12 Bytes of RAM
2025-06-01 Read and set the projector's correct DAC init values for the nextspeed
2025-06-01 Entirely loading and using projector-specific paramaters now
2025-06-01 Introduce DAC init values for both 18 and 24 switchpos and use them as fit
2025-06-02 Disable the DAC for an Auto Cold Start
2025-06-04 Fixing the odd "skip modes while running" bug and the terrible if-redundancy. Also, introducing small font, saves ~4K. Not sure yet if better
2025-06-05 Implements better speed mode switching — no more memcopy of bullshit values.
2025-06-11 Decouple SpeedModes and SpeedConfigs (not all Modes have/need a timer1 config)
2025-06-11 Alig array index and enums toavoid the ugly "-3" hack. Better debug output.
